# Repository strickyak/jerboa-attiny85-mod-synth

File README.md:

# jerboa-attiny85-mod-synth
Modular Synthesizer using an ATtiny85 chip for each module.

See also: http://wiki.yak.net/1132

https://www.youtube.com/results?search_query=jerboa+ATtiny85+modular+synthesizer

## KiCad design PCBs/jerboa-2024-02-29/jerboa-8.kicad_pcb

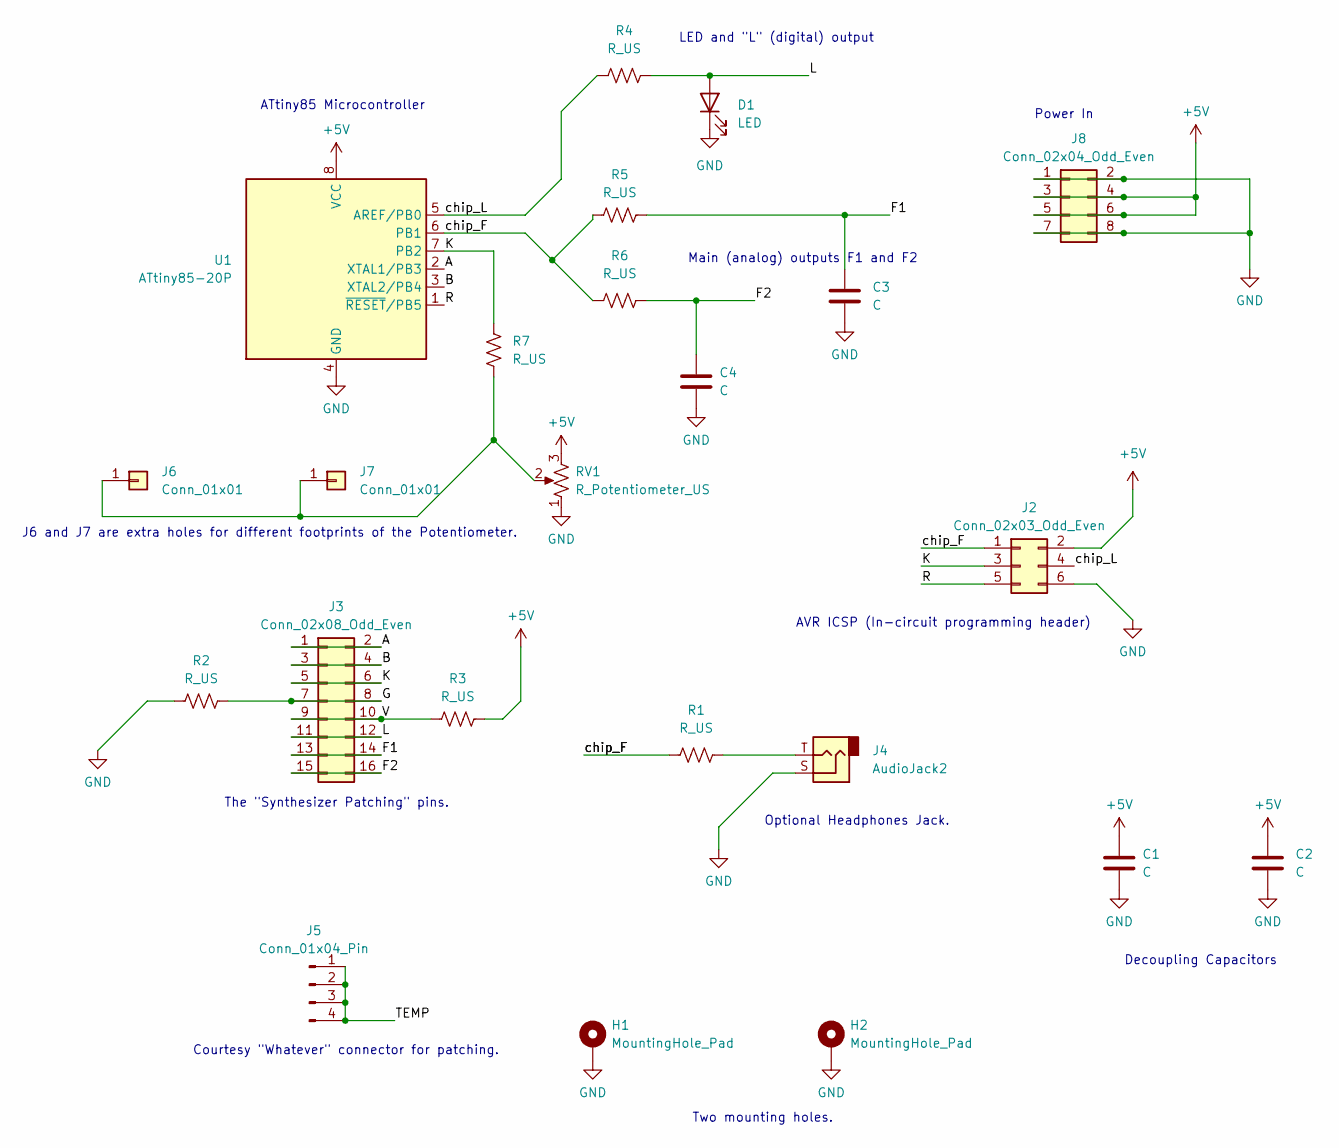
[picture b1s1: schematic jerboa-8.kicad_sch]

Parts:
C1, C2, C3, C4: C; C_Disc_D5.0mm_W2.5mm_P5.00mm
D1: LED; LED_D5.0mm
H1, H2: MountingHole_Pad; MountingHole_4mm_Pad_Via
J2: Conn_02x03_Odd_Even; PinHeader_2x03_P2.54mm_Vertical
J3: Conn_02x08_Odd_Even; PinHeader_2x08_P2.54mm_Vertical
J4: AudioJack2; Jack_3.5mm_CUI_SJ1-3525N_Horizontal_No_Edge_Cuts
J5: Conn_01x04_Pin; PinHeader_1x04_P2.54mm_Vertical
J6, J7: Conn_01x01; PinHeader_1x01_P2.54mm_Vertical
J8: Conn_02x04_Odd_Even; PinHeader_2x04_P2.54mm_Vertical
R1, R2, R3, R4, R5, R6, R7: R_US; R_Axial_DIN0207_L6.3mm_D2.5mm_P10.16mm_Horizontal
RV1: R_Potentiometer_US; Potentiometer_Bourns_3386P_Vertical
U1: ATtiny85-20P; DIP-8_W7.62mm_Socket_LongPads

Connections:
+5V: C1.1, C2.1, J2.2, J8.3, J8.4, J8.5, J8.6, R3.2, RV1.3, U1.8 (VCC)
/A: J3.1, J3.2, U1.2 (XTAL1/PB3)
/B: J3.3, J3.4, U1.3 (XTAL2/PB4)
/F1: C3.1, J3.13, J3.14, R5.2
/F2: C4.1, J3.15, J3.16, R6.2
/G: J3.7, J3.8, R2.2
/K: J2.3, J3.5, J3.6, R7.1, U1.7 (PB2)
/L: D1.2 (A), J3.11, J3.12, R4.2
/R: J2.5, U1.1 (~RESET/PB5)
/TEMP: J5.1, J5.2, J5.3, J5.4
/V: J3.9, J3.10, R3.1
/chip_F: J2.1, R1.1, R5.1, R6.1, U1.6 (PB1)
/chip_L: J2.4, R4.1, U1.5 (AREF/PB0)
GND: C1.2, C2.2, C3.2, C4.2, D1.1 (K), H1.1, H2.1, J2.6, J4.S, J8.1, J8.2, J8.7, J8.8, R2.1, RV1.1, U1.4 (GND)
unnamed: J4.T, R1.2
unnamed: J6.1, J7.1, R7.2, RV1.2

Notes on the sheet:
Two mounting holes.
Power In
AVR ICSP (In-circuit programming header)
Courtesy "Whatever" connector for patching.
Main (analog) outputs F1 and F2
The "Synthesizer Patching" pins.
ATtiny85 Microcontroller
J6 and J7 are extra holes for different footprints of the Potentiometer.
LED and "L" (digital) output
Optional Headphones Jack.
Decoupling Capacitors

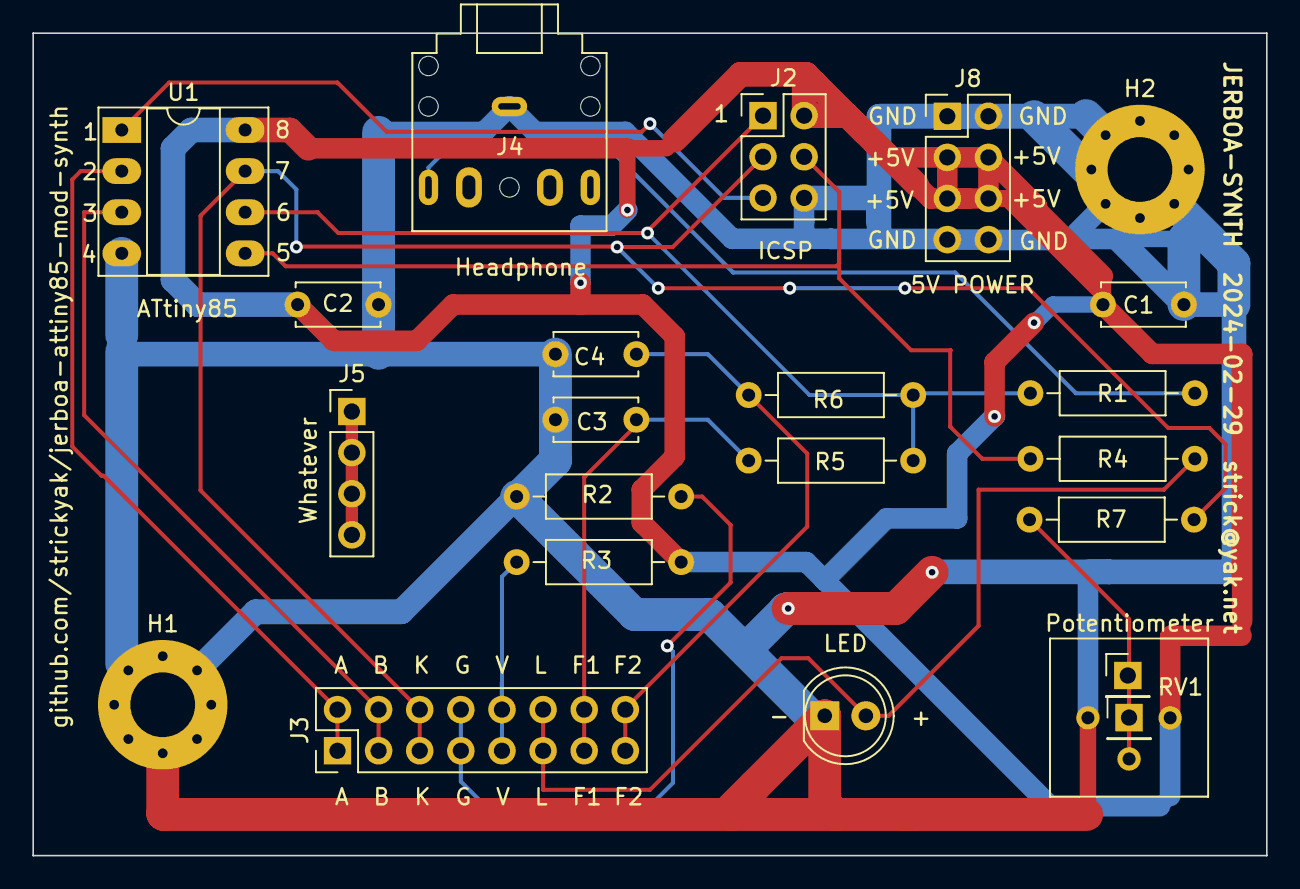
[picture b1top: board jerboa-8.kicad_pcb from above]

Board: 2 copper layers, 76.2 x 50.8 mm, 23 parts (0 on the bottom side), 16 nets.

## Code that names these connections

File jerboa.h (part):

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};
MoctalTicker moc;

// Timer/Counter 1 PWM Output OC1A (PB1)
struct FastPwm1Base {
  static void SetupPLL() {
    // de https://github.com/viking/attiny85-player //
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    OCR1B  = 0;                        // Not used.
    OCR1A  = 128;                      // 50% duty at start

    pinMode(1, OUTPUT);                // Enable PWM output OC1A on pin PB1.
  }
  static void Output(int x) {
    OCR1A = x;  // (p92)
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    OCR1A  = 128;                      // Not used.
    OCR1B  = 128;                      // 50% duty at start

    pinMode(4, OUTPUT);                // Enable PWM output OC1B on pin PB4.
  }
  static void Output(int x) {
    OCR1B = x;  // (p92)
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
struct AnalogIn {
  static void NextInputA() {
    ADMUX = 0 |    // Use Vcc for Reference; disconnect from PB0 (p134)
            _BV(ADLAR) | // Left-Adjust the ADC Result in ADCH (p134)
            3;     // ADC3 is PB3 is A.
  }
  static void NextInputB() {
    ADMUX = 0 |    // Use Vcc for Reference; disconnect from PB0 (p134)
            _BV(ADLAR) | // Left-Adjust the ADC Result in ADCH (p134)
            2;     // ADC2 is PB4 is B.
  }
  static void NextInputK() {
    ADMUX = 0 |    // Use Vcc for Reference; disconnect from PB0 (p134)
            _BV(ADLAR) | // Left-Adjust the ADC Result in ADCH (p134)
            1;     // ADC1 is PB2 is K.
  }
  static void Setup() {
    ADCSRA = _BV(ADEN);  // Enable ADC first.
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
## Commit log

2019-10-27 initial
2019-10-28 demo-master. demo-slave doesn't work.
2019-10-30 work on Slave. pretty-up some stuff.
2019-10-30 remove debugging junk from VFOs
2019-10-31 Now pin K has a knob for input.
2019-11-02 comments about 1V per octave & our range.
2019-11-04 Use knob K in VFA (mult).
2019-11-04 comment mod-mult == VCA.
2019-11-04 Mod rand uses knob K to slow it down.
2019-11-08 MultSigned8xUnsigned8 for 2 quadrant VCA
2019-11-09 Add web links
2019-11-09 Improve ECHO
2019-11-09 Improve RAND
2020-02-09 Sine wave VCO.
2020-02-09 renaming files, adding sin table.
2020-03-08 Better VCF and fix 2-quadrant VCA.
2022-06-14 generated-sin-table.h was left out.
2022-06-14 Basic Envelope. Jesu/joy/mans/desiring vco input.
2024-02-29 add PCBs/jerboa-2024-02-29
2024-03-14 add some NOTES
2024-03-16 mod-slew
